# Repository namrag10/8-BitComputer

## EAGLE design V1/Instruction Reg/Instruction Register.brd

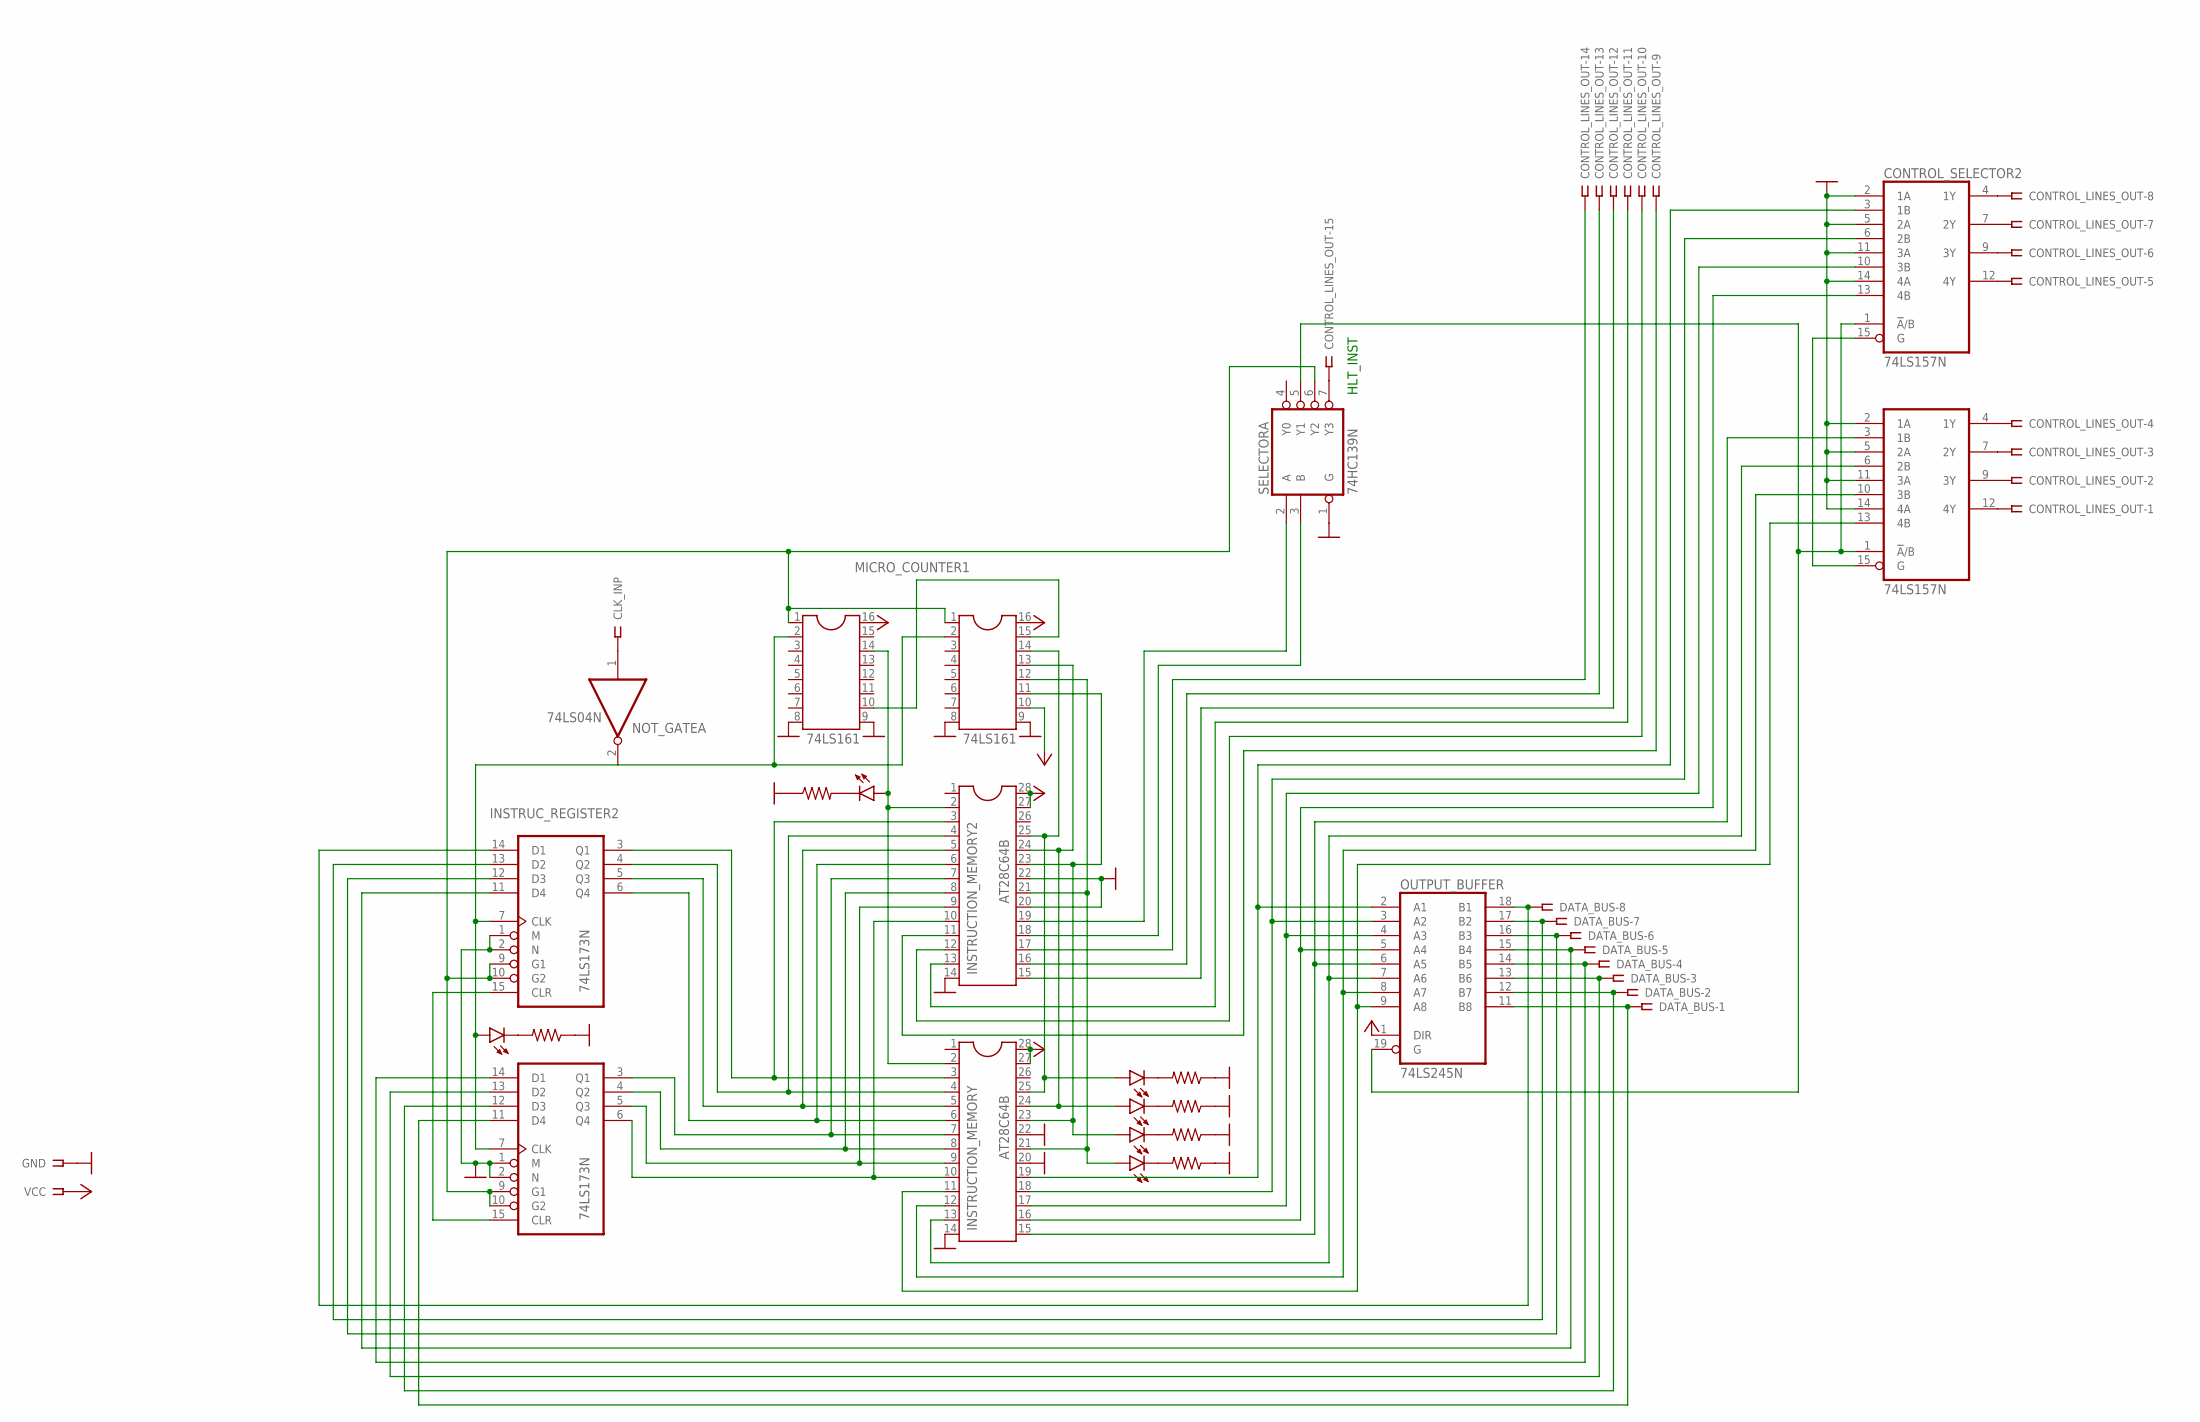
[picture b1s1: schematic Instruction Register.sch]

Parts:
CLK_INP: SSW-101-02-G-S-RA
CONTROL_LINES_OUT: SSW-115-02-G-S
CONTROL_SELECTOR, CONTROL_SELECTOR2: 74LS157N; DIL16
DATA_BUS: SSW-108-02-G-S
GND: SSW-101-02-G-S-RA
INSTRUCTION_MEMORY, INSTRUCTION_MEMORY2: AT28C64B; DIL28-6
INSTRUC_REGISTER2: 74LS173N; DIL16
INVERTED_CLK: LED5MM
I_ADDRESS_REGISTER: 74LS173N; DIL16
LED18, LED19, LED20, LED21, LED22: LED5MM
MICRO_COUNTER, MICRO_COUNTER1: 74LS161; DIL16
NOT_GATE: 74LS04N; DIL14
OUTPUT_BUFFER: 74LS245N; DIL20
R1, R18, R19, R20, R21, R22: ~220; 0204/7
SELECTOR: 74HC139N; DIL16
VCC: SSW-101-02-G-S-RA

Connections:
GND: CONTROL_SELECTOR.2 (1A), CONTROL_SELECTOR.5 (2A), CONTROL_SELECTOR.8 (GND), CONTROL_SELECTOR.11 (3A), CONTROL_SELECTOR.14 (4A), CONTROL_SELECTOR2.2 (1A), CONTROL_SELECTOR2.5 (2A), CONTROL_SELECTOR2.8 (GND), CONTROL_SELECTOR2.11 (3A), CONTROL_SELECTOR2.14 (4A), GND.1, INSTRUCTION_MEMORY.14, INSTRUCTION_MEMORY.20, INSTRUCTION_MEMORY.22, INSTRUCTION_MEMORY2.14, INSTRUCTION_MEMORY2.20, INSTRUCTION_MEMORY2.22, INSTRUC_REGISTER2.1 (M), INSTRUC_REGISTER2.2 (N), INSTRUC_REGISTER2.8 (GND), I_ADDRESS_REGISTER.1 (M), I_ADDRESS_REGISTER.2 (N), I_ADDRESS_REGISTER.8 (GND), MICRO_COUNTER.8, MICRO_COUNTER.9, MICRO_COUNTER1.8, MICRO_COUNTER1.9, NOT_GATE.7 (GND), OUTPUT_BUFFER.10 (GND), R1.1, R18.1, R19.1, R20.1, R21.1, R22.1, SELECTOR.1 (G), SELECTOR.8 (GND)
unnamed: INSTRUCTION_MEMORY.10, INSTRUCTION_MEMORY2.10, I_ADDRESS_REGISTER.6 (Q4)
unnamed: INSTRUCTION_MEMORY.9, INSTRUCTION_MEMORY2.9, I_ADDRESS_REGISTER.5 (Q3)
unnamed: INSTRUCTION_MEMORY.8, INSTRUCTION_MEMORY2.8, I_ADDRESS_REGISTER.4 (Q2)
unnamed: INSTRUCTION_MEMORY.7, INSTRUCTION_MEMORY2.7, I_ADDRESS_REGISTER.3 (Q1)
unnamed: INSTRUCTION_MEMORY.6, INSTRUCTION_MEMORY2.6, INSTRUC_REGISTER2.6 (Q4)
unnamed: INSTRUCTION_MEMORY.5, INSTRUCTION_MEMORY2.5, INSTRUC_REGISTER2.5 (Q3)
unnamed: INSTRUCTION_MEMORY.4, INSTRUCTION_MEMORY2.4, INSTRUC_REGISTER2.4 (Q2)
unnamed: INSTRUCTION_MEMORY.3, INSTRUCTION_MEMORY2.3, INSTRUC_REGISTER2.3 (Q1)
unnamed: CONTROL_LINES_OUT.9, INSTRUCTION_MEMORY2.11
unnamed: CONTROL_SELECTOR.6 (2B), INSTRUCTION_MEMORY.13, OUTPUT_BUFFER.7 (A6)
unnamed: CONTROL_SELECTOR.1 (!A!/B), CONTROL_SELECTOR2.1 (!A!/B), OUTPUT_BUFFER.19 (G), SELECTOR.5 (Y1)
unnamed: CONTROL_SELECTOR.15 (G), CONTROL_SELECTOR2.15 (G)
unnamed: CONTROL_LINES_OUT.1, CONTROL_SELECTOR.12 (4Y)
unnamed: CONTROL_LINES_OUT.2, CONTROL_SELECTOR.9 (3Y)
unnamed: CONTROL_LINES_OUT.3, CONTROL_SELECTOR.7 (2Y)
unnamed: CONTROL_LINES_OUT.4, CONTROL_SELECTOR.4 (1Y)
unnamed: CONTROL_LINES_OUT.5, CONTROL_SELECTOR2.12 (4Y)
unnamed: CONTROL_LINES_OUT.6, CONTROL_SELECTOR2.9 (3Y)
unnamed: CONTROL_LINES_OUT.7, CONTROL_SELECTOR2.7 (2Y)
unnamed: CONTROL_LINES_OUT.8, CONTROL_SELECTOR2.4 (1Y)
unnamed: INSTRUCTION_MEMORY2.19, SELECTOR.2 (A)
unnamed: INSTRUC_REGISTER2.9 (G1), INSTRUC_REGISTER2.10 (G2), I_ADDRESS_REGISTER.9 (G1), I_ADDRESS_REGISTER.10 (G2), MICRO_COUNTER.1, MICRO_COUNTER1.1, SELECTOR.6 (Y2)
unnamed: CONTROL_LINES_OUT.15, SELECTOR.7 (Y3)
unnamed: CLK_INP.1, NOT_GATE.1 (I)
unnamed: INVERTED_CLK.K (C), R1.2
unnamed: DATA_BUS.1, I_ADDRESS_REGISTER.11 (D4), OUTPUT_BUFFER.11 (B8)
unnamed: DATA_BUS.2, I_ADDRESS_REGISTER.12 (D3), OUTPUT_BUFFER.12 (B7)
unnamed: DATA_BUS.3, I_ADDRESS_REGISTER.13 (D2), OUTPUT_BUFFER.13 (B6)
unnamed: DATA_BUS.4, I_ADDRESS_REGISTER.14 (D1), OUTPUT_BUFFER.14 (B5)
unnamed: DATA_BUS.5, INSTRUC_REGISTER2.11 (D4), OUTPUT_BUFFER.15 (B4)
unnamed: DATA_BUS.6, INSTRUC_REGISTER2.12 (D3), OUTPUT_BUFFER.16 (B3)
unnamed: DATA_BUS.7, INSTRUC_REGISTER2.13 (D2), OUTPUT_BUFFER.17 (B2)
unnamed: DATA_BUS.8, INSTRUC_REGISTER2.14 (D1), OUTPUT_BUFFER.18 (B1)
unnamed: CONTROL_SELECTOR.10 (3B), INSTRUCTION_MEMORY.12, OUTPUT_BUFFER.8 (A7)
unnamed: CONTROL_SELECTOR.13 (4B), INSTRUCTION_MEMORY.11, OUTPUT_BUFFER.9 (A8)
unnamed: CONTROL_SELECTOR.3 (1B), INSTRUCTION_MEMORY.15, OUTPUT_BUFFER.6 (A5)
unnamed: CONTROL_SELECTOR2.13 (4B), INSTRUCTION_MEMORY.16, OUTPUT_BUFFER.5 (A4)
unnamed: CONTROL_SELECTOR2.10 (3B), INSTRUCTION_MEMORY.17, OUTPUT_BUFFER.4 (A3)
unnamed: CONTROL_SELECTOR2.6 (2B), INSTRUCTION_MEMORY.18, OUTPUT_BUFFER.3 (A2)
unnamed: CONTROL_SELECTOR2.3 (1B), INSTRUCTION_MEMORY.19, OUTPUT_BUFFER.2 (A1)
unnamed: CONTROL_LINES_OUT.11, INSTRUCTION_MEMORY2.13
unnamed: CONTROL_LINES_OUT.10, INSTRUCTION_MEMORY2.12
unnamed: CONTROL_LINES_OUT.12, INSTRUCTION_MEMORY2.15
unnamed: CONTROL_LINES_OUT.13, INSTRUCTION_MEMORY2.16
unnamed: CONTROL_LINES_OUT.14, INSTRUCTION_MEMORY2.17
unnamed: INSTRUCTION_MEMORY2.18, SELECTOR.3 (B)
unnamed: MICRO_COUNTER.15, MICRO_COUNTER1.10
unnamed: INSTRUCTION_MEMORY.25, INSTRUCTION_MEMORY2.25, LED18.A, MICRO_COUNTER.14
unnamed: INSTRUCTION_MEMORY.24, INSTRUCTION_MEMORY2.24, LED19.A, MICRO_COUNTER.13
unnamed: INSTRUCTION_MEMORY.21, INSTRUCTION_MEMORY2.21, LED21.A, MICRO_COUNTER.12
unnamed: INSTRUCTION_MEMORY.23, INSTRUCTION_MEMORY2.23, LED20.A, MICRO_COUNTER.11
unnamed: INSTRUCTION_MEMORY.2, INSTRUCTION_MEMORY2.2, LED22.A, MICRO_COUNTER1.14
unnamed: INSTRUC_REGISTER2.15 (CLR), I_ADDRESS_REGISTER.15 (CLR)
unnamed: INSTRUC_REGISTER2.7 (CLK), INVERTED_CLK.A, I_ADDRESS_REGISTER.7 (CLK), MICRO_COUNTER.2, MICRO_COUNTER1.2, NOT_GATE.2 (O)
unnamed: LED18.K (C), R18.2
unnamed: LED19.K (C), R19.2
unnamed: LED20.K (C), R20.2
unnamed: LED21.K (C), R21.2
unnamed: LED22.K (C), R22.2
VCC: CONTROL_SELECTOR.16 (VCC), CONTROL_SELECTOR2.16 (VCC), INSTRUCTION_MEMORY.27, INSTRUCTION_MEMORY.28, INSTRUCTION_MEMORY2.27, INSTRUCTION_MEMORY2.28, INSTRUC_REGISTER2.16 (VCC), I_ADDRESS_REGISTER.16 (VCC), MICRO_COUNTER.10, MICRO_COUNTER.16, MICRO_COUNTER1.16, NOT_GATE.14 (VCC), OUTPUT_BUFFER.1 (DIR), OUTPUT_BUFFER.20 (VCC), SELECTOR.16 (VCC), VCC.1

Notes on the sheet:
HLT_INST

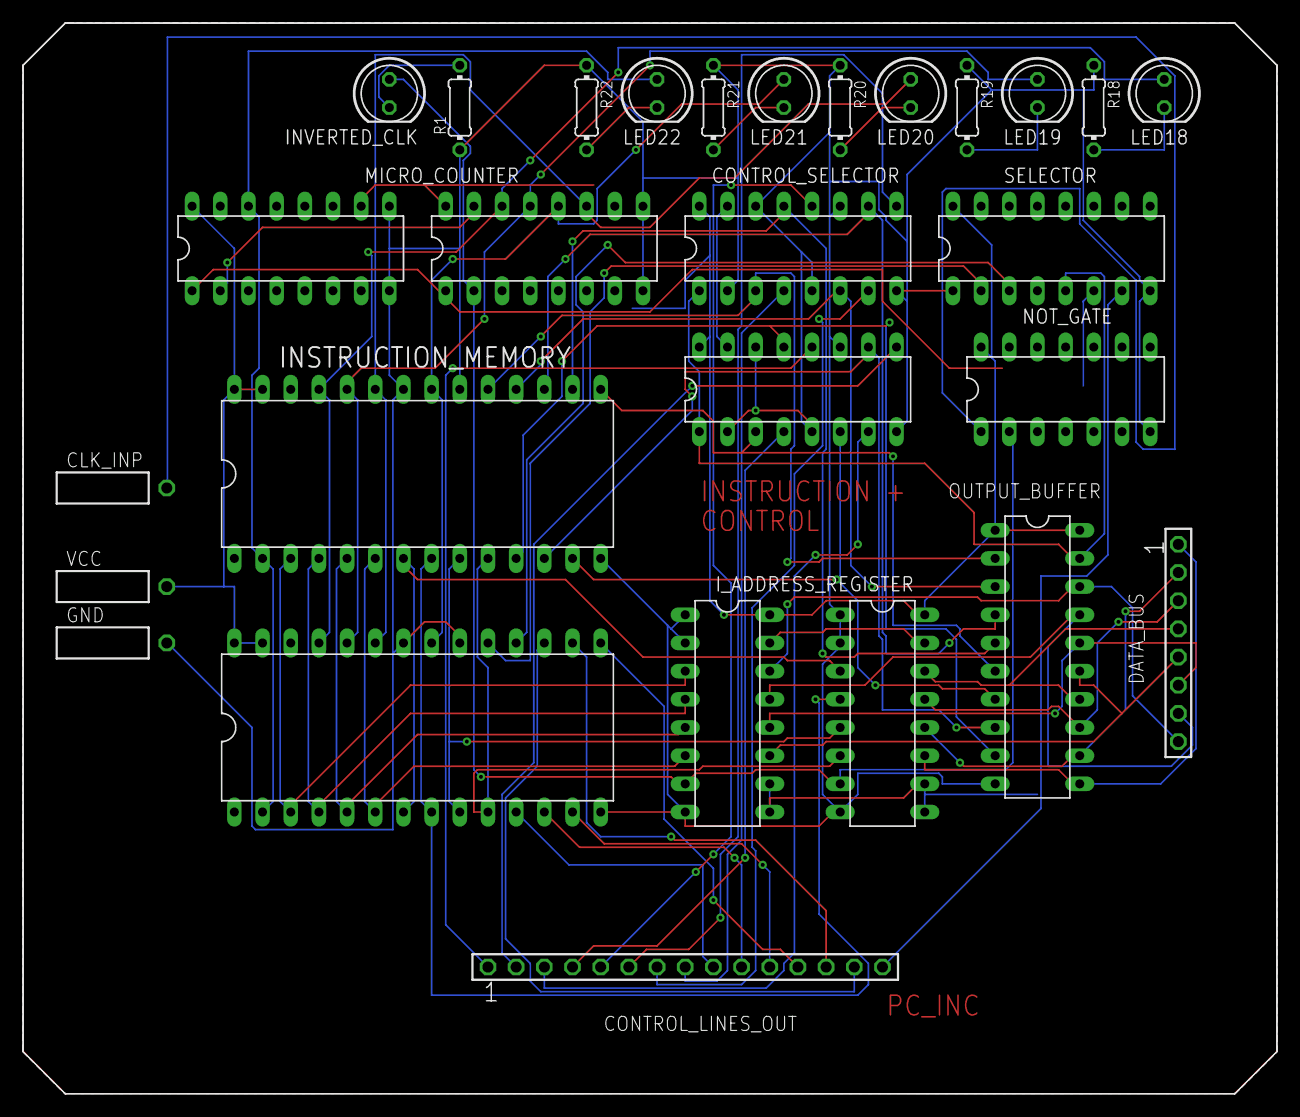
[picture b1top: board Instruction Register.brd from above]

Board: 2 copper layers, 113.0 x 96.5 mm, 28 parts (0 on the bottom side), 61 nets.

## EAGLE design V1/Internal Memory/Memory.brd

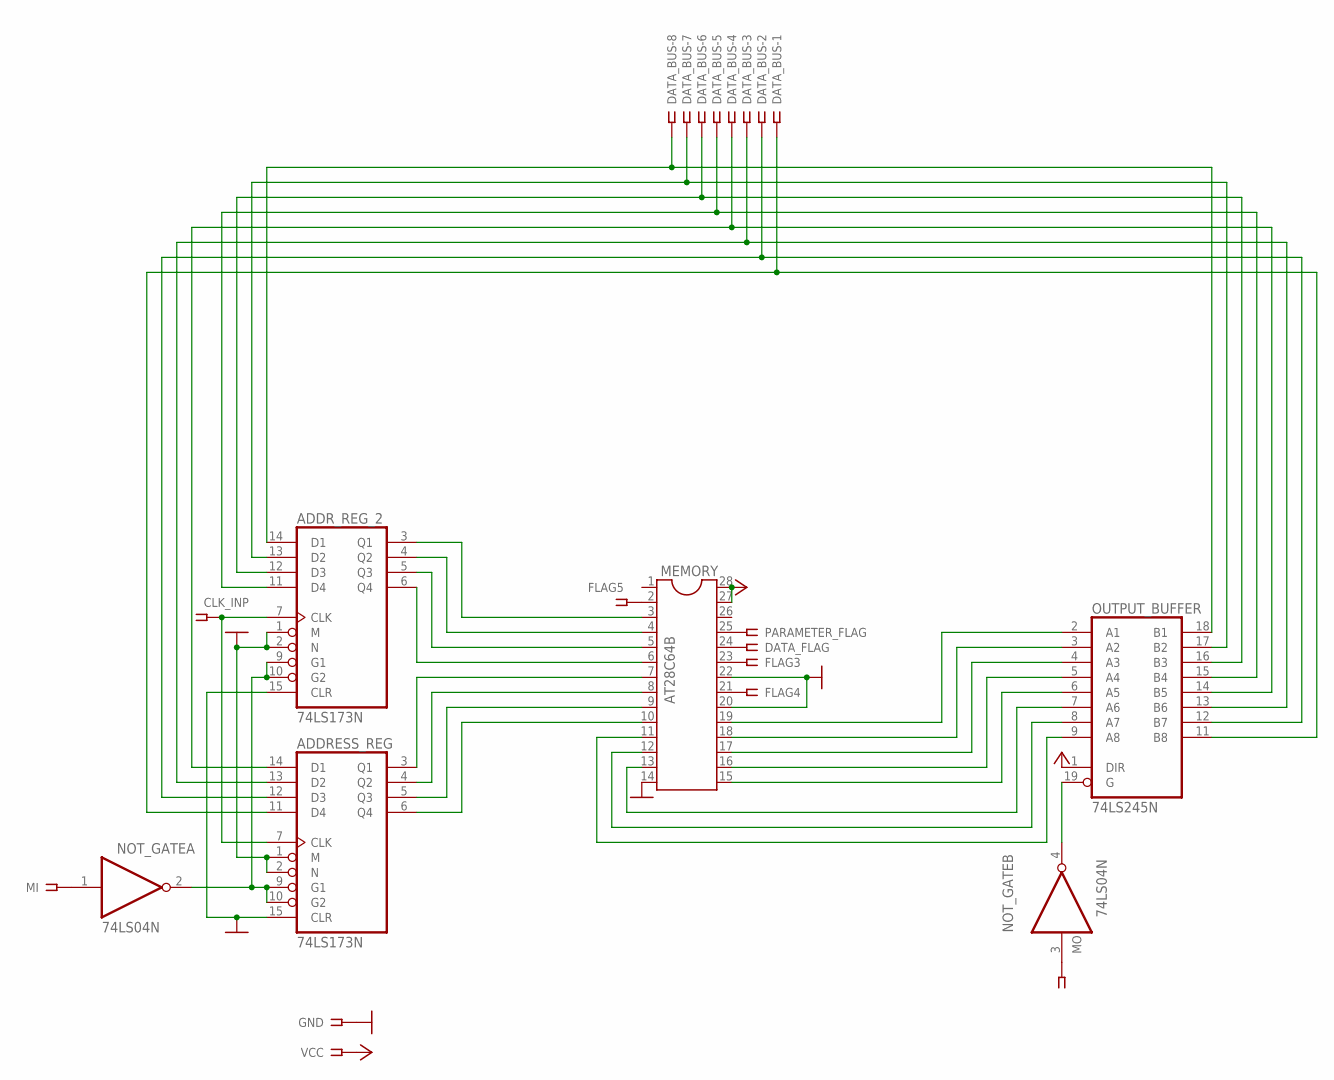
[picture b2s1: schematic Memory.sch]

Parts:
ADDRESS_REG: 74LS173N; DIL16
ADDR_REG_2: 74LS173N; DIL16
CLK_INP: SSW-101-02-G-S-RA
DATA_BUS: SSW-108-02-G-S
DATA_FLAG: SSW-101-02-G-S-RA
FLAG3, FLAG4, FLAG5: SSW-101-02-G-S-RA
GND: SSW-101-02-G-S-RA
MEMORY: AT28C64B; DIL28-6
MI: SSW-101-02-G-S-RA
MO: SSW-101-02-G-S-RA
NOT_GATE: 74LS04N; DIL14
OUTPUT_BUFFER: 74LS245N; DIL20
PARAMETER_FLAG: SSW-101-02-G-S-RA
VCC: SSW-101-02-G-S-RA

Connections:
GND: ADDRESS_REG.1 (M), ADDRESS_REG.2 (N), ADDRESS_REG.8 (GND), ADDRESS_REG.15 (CLR), ADDR_REG_2.1 (M), ADDR_REG_2.2 (N), ADDR_REG_2.8 (GND), ADDR_REG_2.15 (CLR), GND.1, MEMORY.14, MEMORY.20, MEMORY.22, NOT_GATE.7 (GND), OUTPUT_BUFFER.10 (GND)
unnamed: ADDRESS_REG.7 (CLK), ADDR_REG_2.7 (CLK), CLK_INP.1
unnamed: ADDRESS_REG.9 (G1), ADDRESS_REG.10 (G2), ADDR_REG_2.9 (G1), ADDR_REG_2.10 (G2), NOT_GATE.2 (O)
unnamed: MI.1, NOT_GATE.1 (I)
unnamed: ADDRESS_REG.6 (Q4), MEMORY.10
unnamed: ADDRESS_REG.5 (Q3), MEMORY.9
unnamed: ADDRESS_REG.4 (Q2), MEMORY.8
unnamed: ADDRESS_REG.3 (Q1), MEMORY.7
unnamed: ADDR_REG_2.6 (Q4), MEMORY.6
unnamed: FLAG5.1, MEMORY.2
unnamed: FLAG3.1, MEMORY.23
unnamed: DATA_FLAG.1, MEMORY.24
unnamed: MEMORY.25, PARAMETER_FLAG.1
unnamed: FLAG4.1, MEMORY.21
unnamed: ADDR_REG_2.5 (Q3), MEMORY.5
unnamed: ADDR_REG_2.4 (Q2), MEMORY.4
unnamed: ADDR_REG_2.3 (Q1), MEMORY.3
unnamed: MEMORY.13, OUTPUT_BUFFER.7 (A6)
unnamed: MEMORY.12, OUTPUT_BUFFER.8 (A7)
unnamed: MEMORY.11, OUTPUT_BUFFER.9 (A8)
unnamed: MEMORY.15, OUTPUT_BUFFER.6 (A5)
unnamed: MEMORY.16, OUTPUT_BUFFER.5 (A4)
unnamed: MEMORY.17, OUTPUT_BUFFER.4 (A3)
unnamed: MEMORY.18, OUTPUT_BUFFER.3 (A2)
unnamed: MEMORY.19, OUTPUT_BUFFER.2 (A1)
unnamed: MO.1, NOT_GATE.3 (I)
unnamed: NOT_GATE.4 (O), OUTPUT_BUFFER.19 (G)
unnamed: ADDR_REG_2.14 (D1), DATA_BUS.8, OUTPUT_BUFFER.18 (B1)
unnamed: ADDR_REG_2.13 (D2), DATA_BUS.7, OUTPUT_BUFFER.17 (B2)
unnamed: ADDR_REG_2.12 (D3), DATA_BUS.6, OUTPUT_BUFFER.16 (B3)
unnamed: ADDR_REG_2.11 (D4), DATA_BUS.5, OUTPUT_BUFFER.15 (B4)
unnamed: ADDRESS_REG.14 (D1), DATA_BUS.4, OUTPUT_BUFFER.14 (B5)
unnamed: ADDRESS_REG.13 (D2), DATA_BUS.3, OUTPUT_BUFFER.13 (B6)
unnamed: ADDRESS_REG.12 (D3), DATA_BUS.2, OUTPUT_BUFFER.12 (B7)
unnamed: ADDRESS_REG.11 (D4), DATA_BUS.1, OUTPUT_BUFFER.11 (B8)
VCC: ADDRESS_REG.16 (VCC), ADDR_REG_2.16 (VCC), MEMORY.27, MEMORY.28, NOT_GATE.14 (VCC), OUTPUT_BUFFER.1 (DIR), OUTPUT_BUFFER.20 (VCC), VCC.1

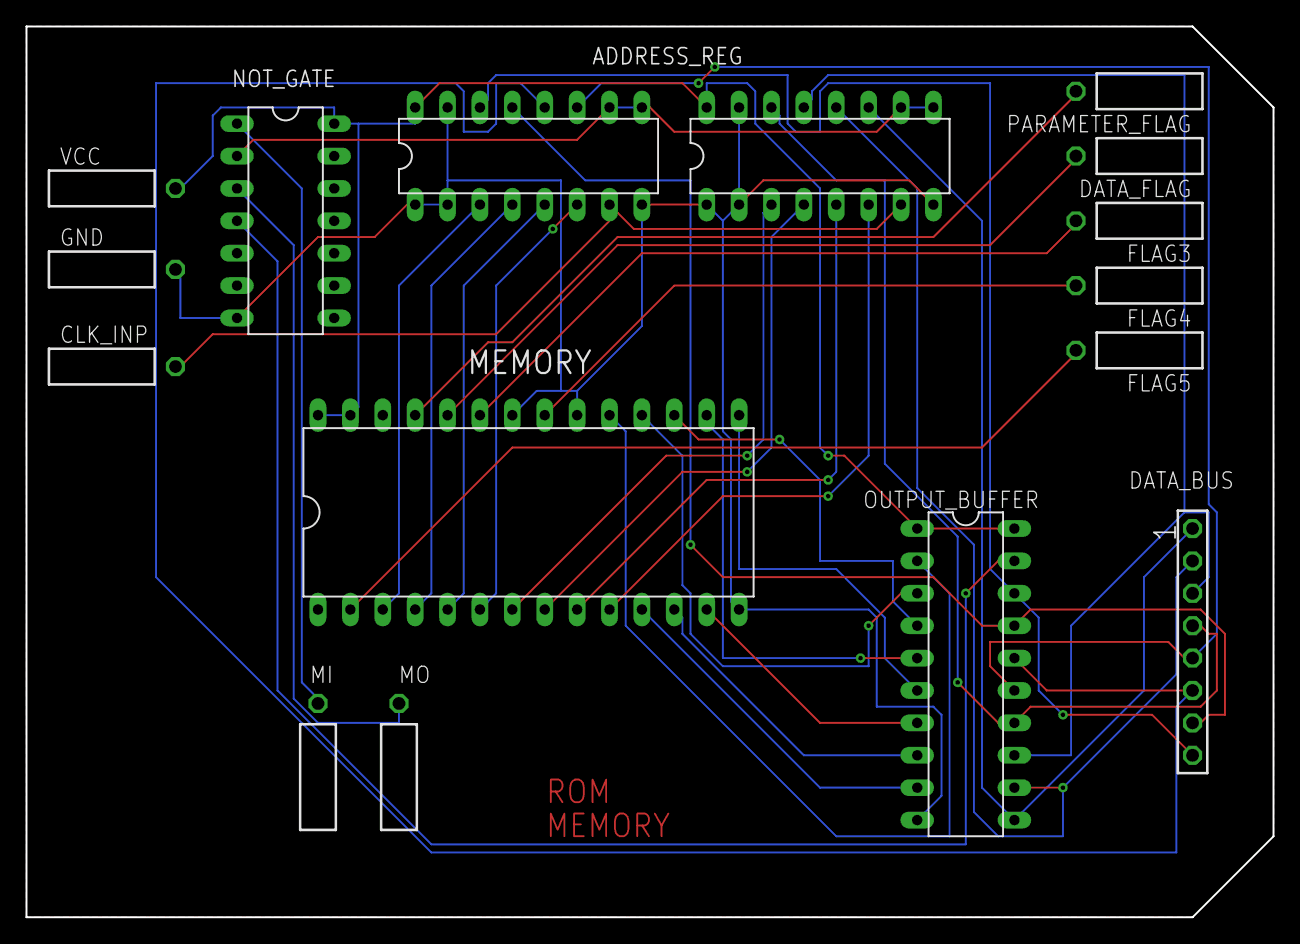
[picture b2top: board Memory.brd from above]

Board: 2 copper layers, 97.8 x 69.8 mm, 16 parts (0 on the bottom side), 36 nets.

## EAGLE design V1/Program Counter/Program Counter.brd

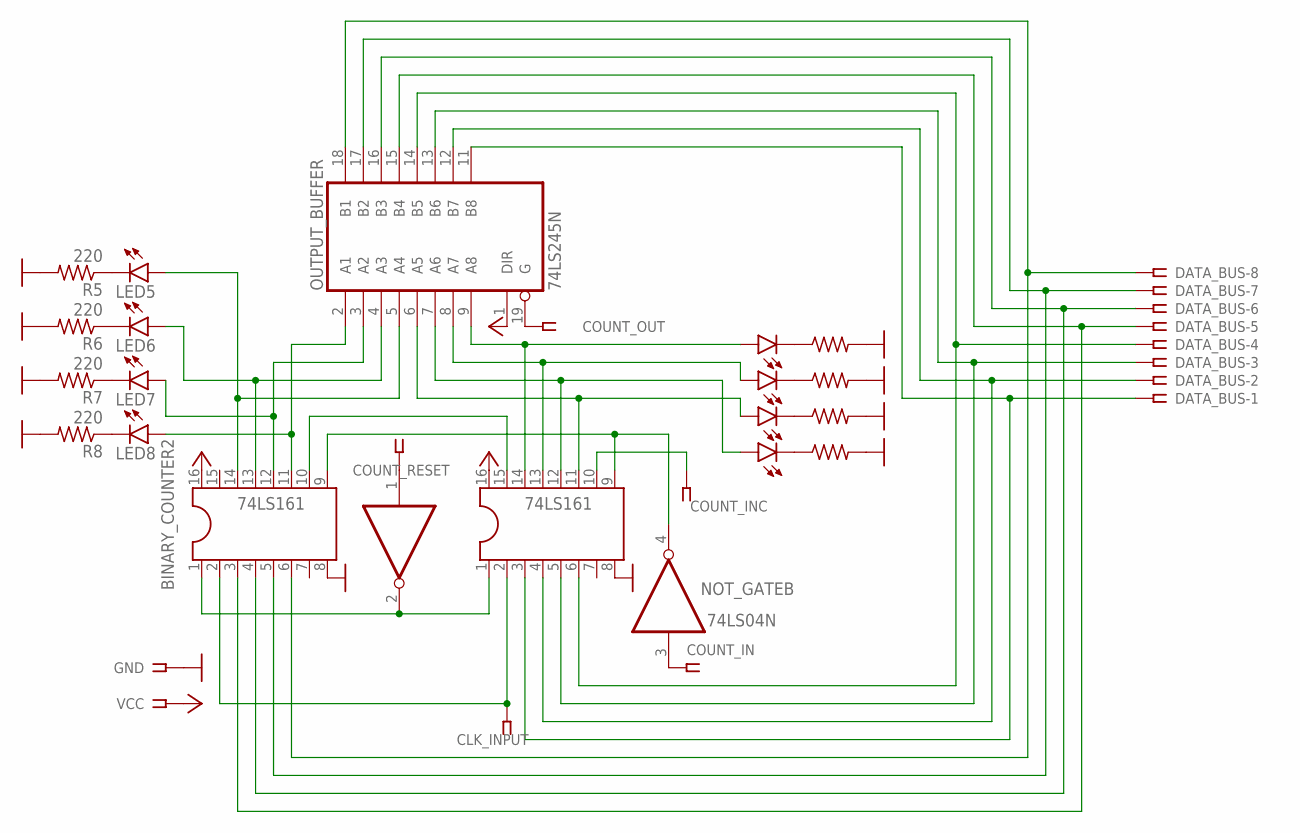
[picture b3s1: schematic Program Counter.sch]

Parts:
BINARY_COUNTER, BINARY_COUNTER2: 74LS161; DIL16
CLK_INPUT: SSW-101-02-G-S-RA
COUNT_IN: SSW-101-02-G-S-RA
COUNT_INC: SSW-101-02-G-S-RA
COUNT_OUT: SSW-101-02-G-S-RA
COUNT_RESET: SSW-101-02-G-S-RA
DATA_BUS: SSW-108-02-G-S
GND: SSW-101-02-G-S-RA
LED1, LED2, LED3, LED4, LED5, LED6, LED7, LED8: LED5MM
NOT_GATE: 74LS04N; DIL14
OUTPUT_BUFFER: 74LS245N; DIL20
R1, R2, R3, R4, R5, R6, R7, R8: 220; 0204/7
VCC: SSW-101-02-G-S-RA

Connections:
GND: BINARY_COUNTER.8, BINARY_COUNTER2.8, GND.1, NOT_GATE.7 (GND), OUTPUT_BUFFER.10 (GND), R1.2, R2.2, R3.2, R4.2, R5.2, R6.2, R7.2, R8.2
unnamed: BINARY_COUNTER.2, BINARY_COUNTER2.2, CLK_INPUT.1
unnamed: BINARY_COUNTER.1, BINARY_COUNTER2.1, NOT_GATE.2 (O)
unnamed: LED1.K (C), R1.1
unnamed: BINARY_COUNTER.9, BINARY_COUNTER2.9, NOT_GATE.4 (O)
unnamed: BINARY_COUNTER.10, COUNT_INC.1
unnamed: BINARY_COUNTER.15, BINARY_COUNTER2.10
unnamed: BINARY_COUNTER.14, LED1.A, OUTPUT_BUFFER.9 (A8)
unnamed: BINARY_COUNTER.13, LED2.A, OUTPUT_BUFFER.8 (A7)
unnamed: BINARY_COUNTER.12, LED3.A, OUTPUT_BUFFER.7 (A6)
unnamed: BINARY_COUNTER.11, LED4.A, OUTPUT_BUFFER.6 (A5)
unnamed: BINARY_COUNTER2.11, LED8.A, OUTPUT_BUFFER.2 (A1)
unnamed: COUNT_RESET.1, NOT_GATE.1 (I)
unnamed: BINARY_COUNTER2.13, LED6.A, OUTPUT_BUFFER.4 (A3)
unnamed: COUNT_IN.1, NOT_GATE.3 (I)
unnamed: BINARY_COUNTER.3, DATA_BUS.1, OUTPUT_BUFFER.11 (B8)
unnamed: BINARY_COUNTER.4, DATA_BUS.2, OUTPUT_BUFFER.12 (B7)
unnamed: BINARY_COUNTER.5, DATA_BUS.3, OUTPUT_BUFFER.13 (B6)
unnamed: BINARY_COUNTER.6, DATA_BUS.4, OUTPUT_BUFFER.14 (B5)
unnamed: BINARY_COUNTER2.3, DATA_BUS.5, OUTPUT_BUFFER.15 (B4)
unnamed: BINARY_COUNTER2.4, DATA_BUS.6, OUTPUT_BUFFER.16 (B3)
unnamed: BINARY_COUNTER2.5, DATA_BUS.7, OUTPUT_BUFFER.17 (B2)
unnamed: BINARY_COUNTER2.6, DATA_BUS.8, OUTPUT_BUFFER.18 (B1)
unnamed: LED2.K (C), R2.1
unnamed: LED3.K (C), R3.1
unnamed: LED4.K (C), R4.1
unnamed: LED5.K (C), R5.1
unnamed: LED6.K (C), R6.1
unnamed: LED7.K (C), R7.1
unnamed: LED8.K (C), R8.1
unnamed: COUNT_OUT.1, OUTPUT_BUFFER.19 (G)
unnamed: BINARY_COUNTER2.12, LED7.A, OUTPUT_BUFFER.3 (A2)
unnamed: BINARY_COUNTER2.14, LED5.A, OUTPUT_BUFFER.5 (A4)
VCC: BINARY_COUNTER.16, BINARY_COUNTER2.16, NOT_GATE.14 (VCC), OUTPUT_BUFFER.1 (DIR), OUTPUT_BUFFER.20 (VCC), VCC.1

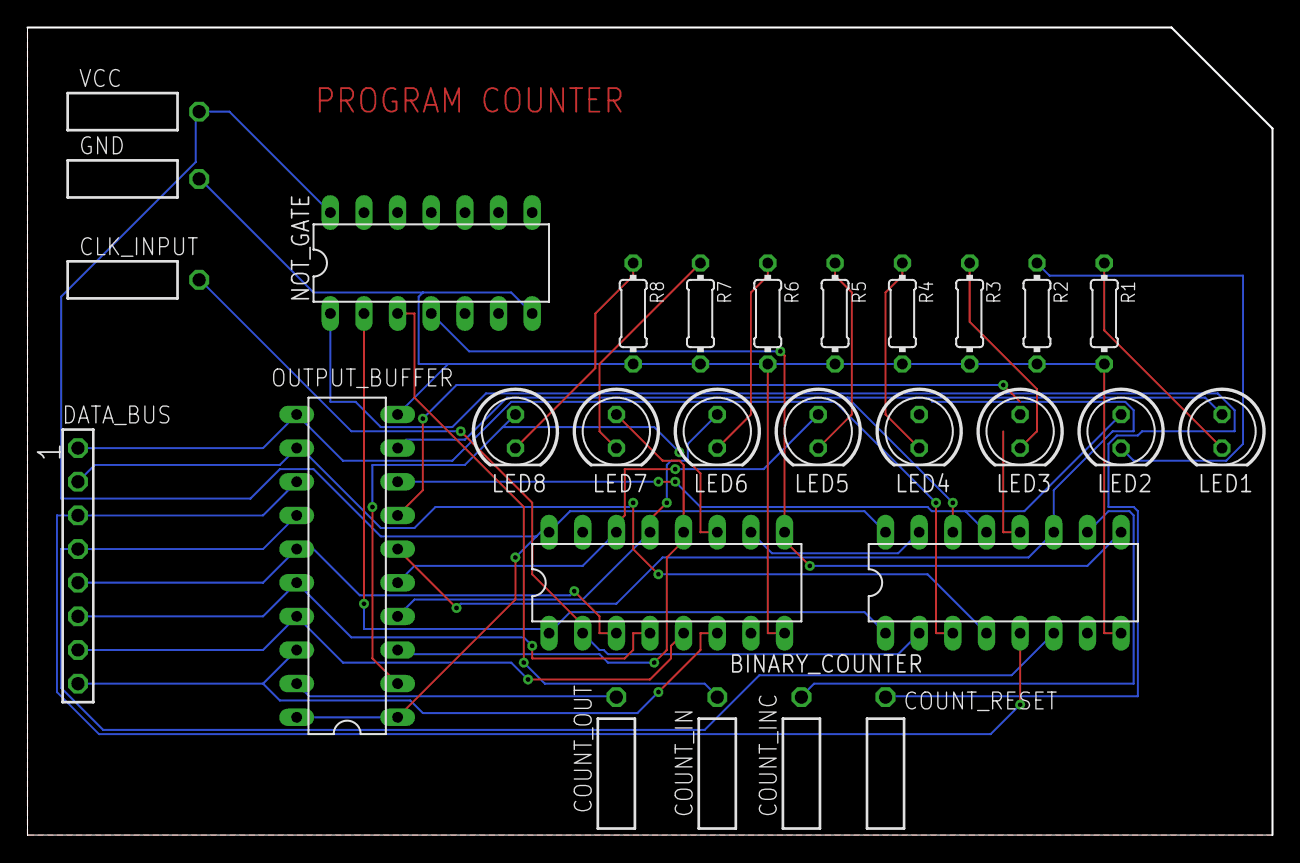
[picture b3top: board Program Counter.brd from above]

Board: 2 copper layers, 94.0 x 61.0 mm, 28 parts (0 on the bottom side), 34 nets.

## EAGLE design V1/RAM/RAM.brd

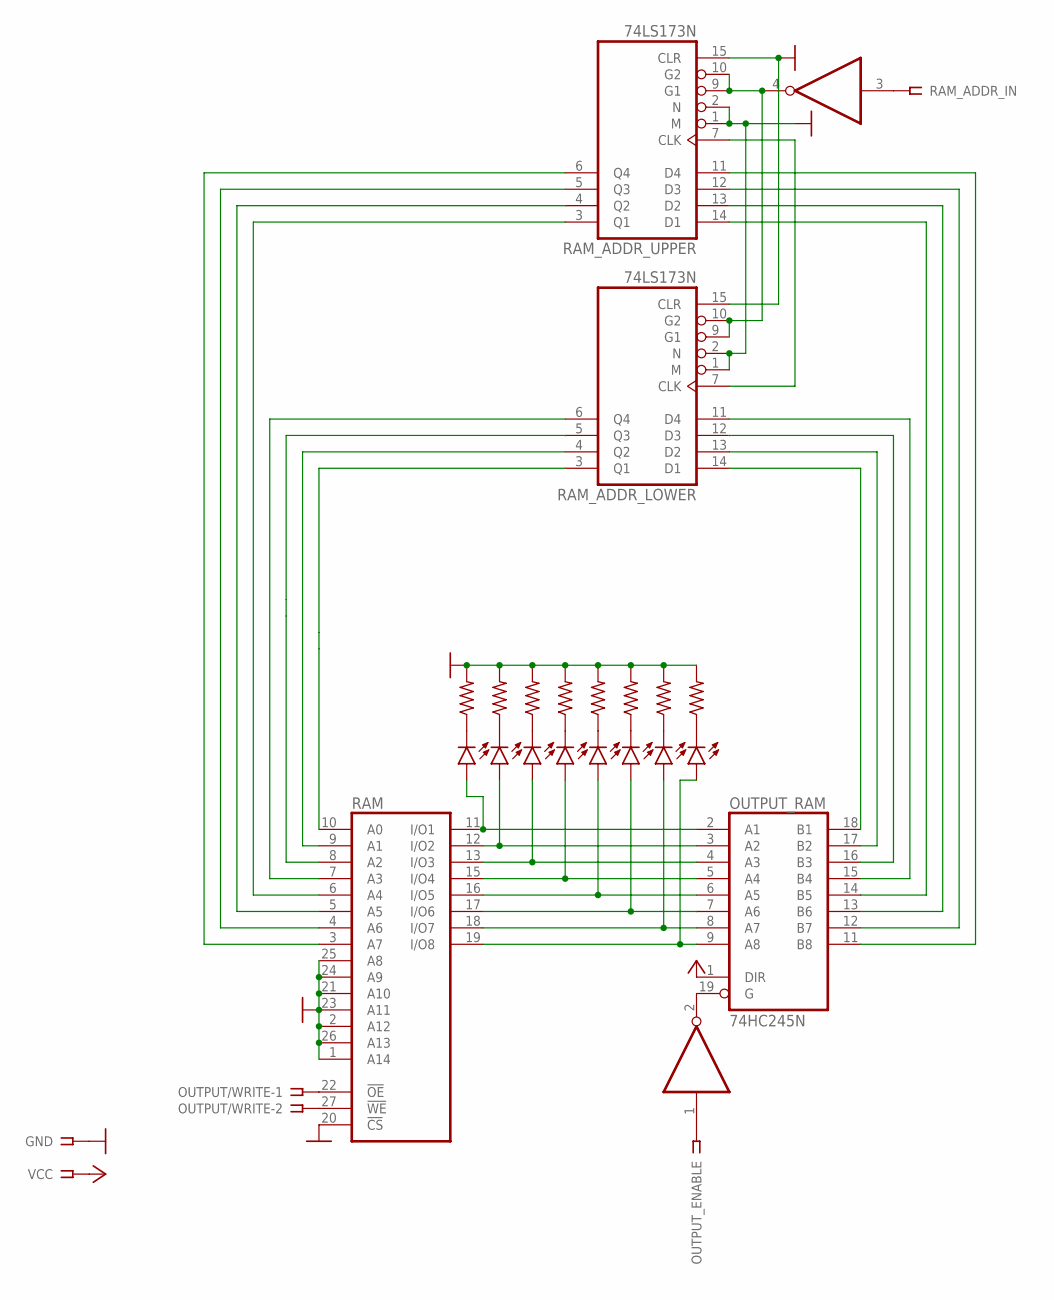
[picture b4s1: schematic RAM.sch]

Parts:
GND: SSW-101-02-G-S-RA
LED1, LED2, LED3, LED4, LED5, LED6, LED7, LED8: LED3MM
NOT_GATE: 74LS04N; DIL14
OUTPUT/WRITE: SSW-102-02-G-S
OUTPUT_ENABLE: SSW-101-02-G-S
OUTPUT_RAM: 74HC245N; DIL20
R1, R2, R3, R4, R5, R6, R7, R8: R-US_0204/7; 0204/7
RAM: 71256P; DIL28-6
RAM_ADDR_IN: SSW-101-02-G-S
RAM_ADDR_LOWER: 74LS173N; DIL16
RAM_ADDR_UPPER: 74LS173N; DIL16
VCC: SSW-101-02-G-S-RA

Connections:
GND: GND.1, NOT_GATE.7 (GND), OUTPUT_RAM.10 (GND), R1.2, R2.2, R3.2, R4.2, R5.2, R6.2, R7.2, R8.2, RAM.1 (A14), RAM.2 (A12), RAM.14 (GND), RAM.20 (!CS), RAM.21 (A10), RAM.23 (A11), RAM.24 (A9), RAM.25 (A8), RAM.26 (A13), RAM_ADDR_LOWER.1 (M), RAM_ADDR_LOWER.2 (N), RAM_ADDR_LOWER.8 (GND), RAM_ADDR_LOWER.15 (CLR), RAM_ADDR_UPPER.1 (M), RAM_ADDR_UPPER.2 (N), RAM_ADDR_UPPER.8 (GND), RAM_ADDR_UPPER.15 (CLR)
unnamed: LED8.A, OUTPUT_RAM.2 (A1), RAM.11 (I/O1)
unnamed: LED1.A, OUTPUT_RAM.3 (A2), RAM.12 (I/O2)
unnamed: LED2.A, OUTPUT_RAM.4 (A3), RAM.13 (I/O3)
unnamed: LED3.A, OUTPUT_RAM.5 (A4), RAM.15 (I/O4)
unnamed: LED4.A, OUTPUT_RAM.6 (A5), RAM.16 (I/O5)
unnamed: LED5.A, OUTPUT_RAM.7 (A6), RAM.17 (I/O6)
unnamed: LED6.A, OUTPUT_RAM.8 (A7), RAM.18 (I/O7)
unnamed: LED7.A, OUTPUT_RAM.9 (A8), RAM.19 (I/O8)
unnamed: LED1.K (C), R1.1
unnamed: LED2.K (C), R2.1
unnamed: LED3.K (C), R3.1
unnamed: LED4.K (C), R4.1
unnamed: LED5.K (C), R5.1
unnamed: LED6.K (C), R6.1
unnamed: LED7.K (C), R7.1
unnamed: LED8.K (C), R8.1
unnamed: OUTPUT_RAM.18 (B1), RAM_ADDR_LOWER.14 (D1)
unnamed: OUTPUT_RAM.17 (B2), RAM_ADDR_LOWER.13 (D2)
unnamed: OUTPUT_RAM.16 (B3), RAM_ADDR_LOWER.12 (D3)
unnamed: OUTPUT_RAM.15 (B4), RAM_ADDR_LOWER.11 (D4)
unnamed: OUTPUT_RAM.14 (B5), RAM_ADDR_UPPER.14 (D1)
unnamed: OUTPUT_RAM.13 (B6), RAM_ADDR_UPPER.13 (D2)
unnamed: OUTPUT_RAM.12 (B7), RAM_ADDR_UPPER.12 (D3)
unnamed: RAM.3 (A7), RAM_ADDR_UPPER.6 (Q4)
unnamed: NOT_GATE.2 (O), OUTPUT_RAM.19 (G)
unnamed: OUTPUT/WRITE.1, RAM.22 (!OE)
unnamed: OUTPUT/WRITE.2, RAM.27 (!WE)
unnamed: NOT_GATE.1 (I), OUTPUT_ENABLE.1
unnamed: NOT_GATE.3 (I), RAM_ADDR_IN.1
unnamed: NOT_GATE.4 (O), RAM_ADDR_LOWER.9 (G1), RAM_ADDR_LOWER.10 (G2), RAM_ADDR_UPPER.9 (G1), RAM_ADDR_UPPER.10 (G2)
unnamed: RAM.10 (A0), RAM_ADDR_LOWER.3 (Q1)
unnamed: RAM.9 (A1), RAM_ADDR_LOWER.4 (Q2)
unnamed: RAM.8 (A2), RAM_ADDR_LOWER.5 (Q3)
unnamed: RAM.7 (A3), RAM_ADDR_LOWER.6 (Q4)
unnamed: RAM.6 (A4), RAM_ADDR_UPPER.3 (Q1)
unnamed: RAM.5 (A5), RAM_ADDR_UPPER.4 (Q2)
unnamed: RAM.4 (A6), RAM_ADDR_UPPER.5 (Q3)
unnamed: OUTPUT_RAM.11 (B8), RAM_ADDR_UPPER.11 (D4)
unnamed: RAM_ADDR_LOWER.7 (CLK), RAM_ADDR_UPPER.7 (CLK)
VCC: NOT_GATE.14 (VCC), OUTPUT_RAM.1 (DIR), OUTPUT_RAM.20 (VCC), RAM.28 (VCC), RAM_ADDR_LOWER.16 (VCC), RAM_ADDR_UPPER.16 (VCC), VCC.1

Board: 2 copper layers, 26 parts (0 on the bottom side), 41 nets, no tracks yet.
